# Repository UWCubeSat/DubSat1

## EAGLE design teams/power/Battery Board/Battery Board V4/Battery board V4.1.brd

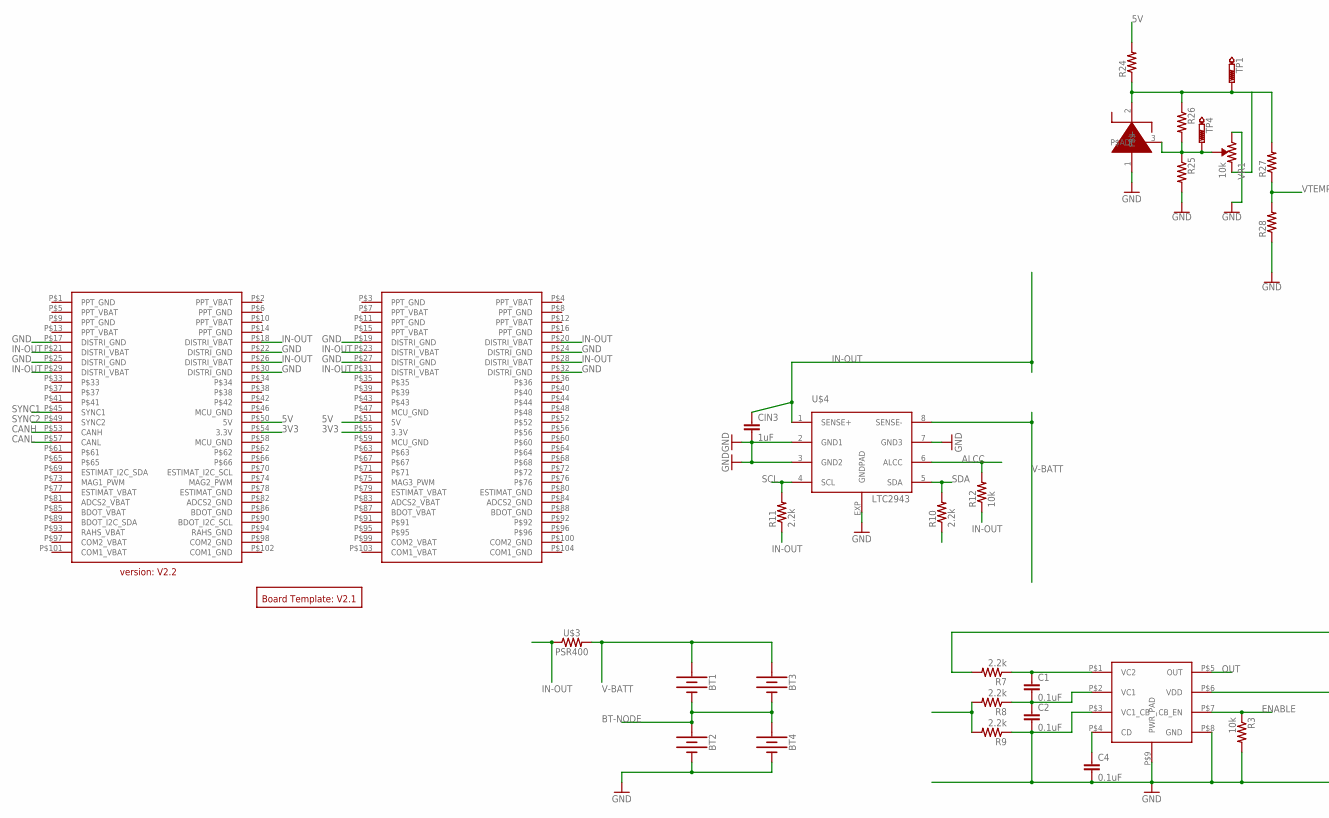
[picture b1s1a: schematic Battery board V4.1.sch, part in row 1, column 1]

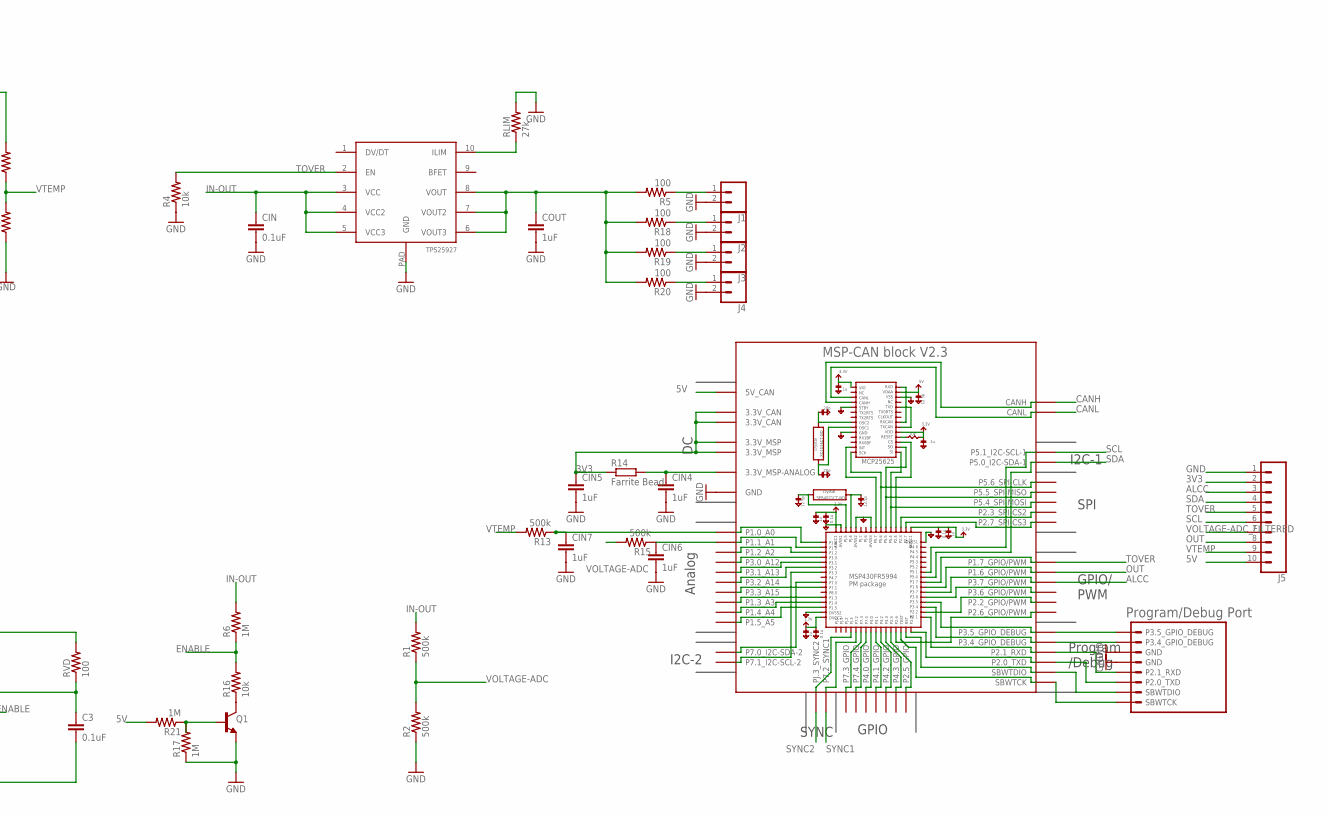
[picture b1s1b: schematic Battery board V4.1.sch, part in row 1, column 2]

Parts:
BT1, BT2, BT3, BT4: BATTERY-18650; BATTERY_18650-HOLDER
C1, C2, C3, C4: 0.1uF; C0805
CIN: 0.1uF; C0805
CIN3, CIN4, CIN5, CIN6, CIN7: 1uF; C0805
COUT: 1uF; C0805
J1, J2, J3, J4: CONN_02PTH3; 1X02_LONGPADS
J5: CONN_10LOCK; 1X10_LOCK
Q1: TRANS_NPN-MMBT2222AL; SOT23-3
R1, R2, R13, R15: 500k; R0805
R3, R4, R12, R16: 10k; R0805
R5, R18, R19, R20: 100; R0805
R6: 1M; R0805
R7, R8, R9, R10, R11: 2.2k; R0805
R14: Farrite Bead; R1206
R17, R21: 1M; M0805
R24, R25, R26, R27, R28: R-US_R0805; R0805
RLIM: 27k; R0805
RVD: 100; R0805
TP1, TP4: PTR1PAD1-13Y; P1-13Y
U$1: MSP-CAN_BLOCK
U$2: PROGRAM/DEBUG_PORT; 1X08_CONNECTOR
U$3: PSR400
U$4: LTC2943; DFN8(3X3)LT
U$5: TPS252927; VSON10
U$7: 2X26_CONNECTOR_(V2.2); 4X26_CONNECTOR_(V2.2)
U$8: BQ29209; VSON8
U$9: BOARD_TEMPLATE_(V2.1)
U$10: LM135Z; TO-92-3
VR1: 10k; TRIMPOT-SMD-TC33X

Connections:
3V3: CIN5.1, J5.2, R14.1, U$1.3.3V@CAN1 (3.3V_CAN), U$1.3.3V@CAN2 (3.3V_CAN), U$1.3.3V@MSP1 (3.3V_MSP), U$1.3.3V@MSP2 (3.3V_MSP), U$7.P$54 (3.3V), U$7.P$55 (3.3V)
5V: J5.10, R21.2, R24.2, U$1.5V (5V_CAN), U$7.P$50 (5V), U$7.P$51 (5V)
ALCC: J5.3, R12.2, U$1.P3.7_GPIO/PWM, U$4.6 (ALCC)
BASE: Q1.1 (B), R17.2, R21.1
BT-NODE: BT1.GND@1 (-), BT2.PWR@1 (+), BT3.GND@1 (-), BT4.PWR@1 (+), R8.2, R9.2
CANH: U$1.CANH, U$7.P$53 (CANH)
CANL: U$1.CANL, U$7.P$57 (CANL)
ENABLE: R3.1, R6.1, R16.2, U$8.P$7 (CB_EN)
FERRITE-BEAD: CIN4.1, R14.2, U$1.3.3V_ANALOG@MSP2 (3.3V_MSP-ANALOG)
GND: BT2.GND@1 (-), BT4.GND@1 (-), C2.2, C3.2, C4.2, CIN.2, CIN3.2, CIN4.2, CIN5.2, CIN6.2, CIN7.2, COUT.2, J1.2, J2.2, J3.2, J4.2, J5.1, Q1.2 (E), R2.1, R3.2, R4.1, R9.1, R17.1, R25.2, R28.1, RLIM.2, U$1.GND@1 (GND), U$1.GND@2 (GND), U$1.GND@3 (GND), U$1.GND@4 (GND), U$1.GND@5 (GND), U$1.GND@7 (GND), U$1.GND@8 (GND), U$1.GND@9 (GND), U$1.GND@10 (GND), U$1.GND@11 (GND), U$1.GND@12 (GND), U$1.GND@13 (GND), U$1.GND@14 (GND), U$1.GND@15 (GND), U$1.GND@16 (GND), U$1.GND@17 (GND), U$1.GND@26 (GND), U$2.5 (GND), U$2.6 (GND), U$4.2 (GND1), U$4.3 (GND2), U$4.7 (GND3), U$4.EXP (GNDPAD), U$5.PAD (GND), U$7.P$17 (DISTRI_GND), U$7.P$19 (DISTRI_GND), U$7.P$22 (DISTRI_GND), U$7.P$24 (DISTRI_GND), U$7.P$25 (DISTRI_GND), U$7.P$27 (DISTRI_GND), U$7.P$30 (DISTRI_GND), U$7.P$32 (DISTRI_GND), U$8.P$3 (VC1_CB), U$8.P$8 (GND), U$8.P$9 (PWR_PAD), U$10.1 (P$-), VR1.1 (CW)
HEATER1: J3.1, R19.1
IN-OUT: CIN.1, CIN3.1, R1.2, R6.2, R7.2, R10.1, R11.1, R12.1, RVD.2, U$3.P$1 (1), U$4.1 (SENSE+), U$5.3 (VCC), U$5.4 (VCC2), U$5.5 (VCC3), U$7.P$18 (DISTRI_VBAT), U$7.P$20 (DISTRI_VBAT), U$7.P$21 (DISTRI_VBAT), U$7.P$23 (DISTRI_VBAT), U$7.P$26 (DISTRI_VBAT), U$7.P$28 (DISTRI_VBAT), U$7.P$29 (DISTRI_VBAT), U$7.P$31 (DISTRI_VBAT)
unnamed: J1.1, R5.1
unnamed: C1.1, R7.1, U$8.P$1 (VC2)
unnamed: C1.2, C2.1, R8.1, U$8.P$2 (VC1)
unnamed: C3.1, RVD.1, U$8.P$6 (VDD)
unnamed: Q1.3 (C), R16.1
unnamed: C4.1, U$8.P$4 (CD)
unnamed: COUT.1, R5.2, R18.2, R19.2, R20.2, U$5.6 (VOUT3), U$5.7 (VOUT2), U$5.8 (VOUT)
unnamed: RLIM.1, U$5.10 (ILIM)
unnamed: J2.1, R18.1
unnamed: J4.1, R20.1
unnamed: U$1.P3.5_GPIO_DEBUG, U$2.8 (P3.5_GPIO_DEBUG)
unnamed: U$1.P3.4_GPIO_DEBUG, U$2.7 (P3.4_GPIO_DEBUG)
unnamed: U$1.P2.1_RXD, U$2.4 (P2.1_RXD)
unnamed: U$1.P2.0_TXD, U$2.3 (P2.0_TXD)
unnamed: U$1.SBWTDIO, U$2.2 (SBWTDIO)
unnamed: U$1.SBWTCK, U$2.SBWTCK
unnamed: R24.1, R26.1, R27.2, TP1.TP, U$10.2 (P$+), VR1.3 (CCW)
unnamed: R25.1, R26.2, TP4.TP, U$10.3 (P$ADJ), VR1.2 (WIPER)
OUT: J5.8, U$1.P1.6_GPIO/PWM, U$8.P$5 (OUT)
SCL: J5.6, R11.2, U$1.P5.1_I2C-SCL-1, U$4.4 (SCL)
SDA: J5.4, R10.2, U$1.P5.0_I2C-SDA-1, U$4.5 (SDA)
SYNC1: U$1.P7.2_SYNC1, U$7.P$45 (SYNC1)
SYNC2: U$1.PJ.3_SYNC2, U$7.P$49 (SYNC2)
TOVER: J5.5, R4.2, U$1.P1.7_GPIO/PWM, U$5.2 (EN)
V-BATT: BT1.PWR@1 (+), BT3.PWR@1 (+), U$3.P$2 (2), U$4.8 (SENSE-)
VOLTAGE-ADC: R1.1, R2.2, R15.2
VOLTAGE-ADC_FILTERED: CIN6.1, J5.7, R15.1, U$1.P1.1_A1
VTEMP: J5.9, R13.2, R27.1, R28.2
VTEMP_FILTERED: CIN7.1, R13.1, U$1.P1.0_A0

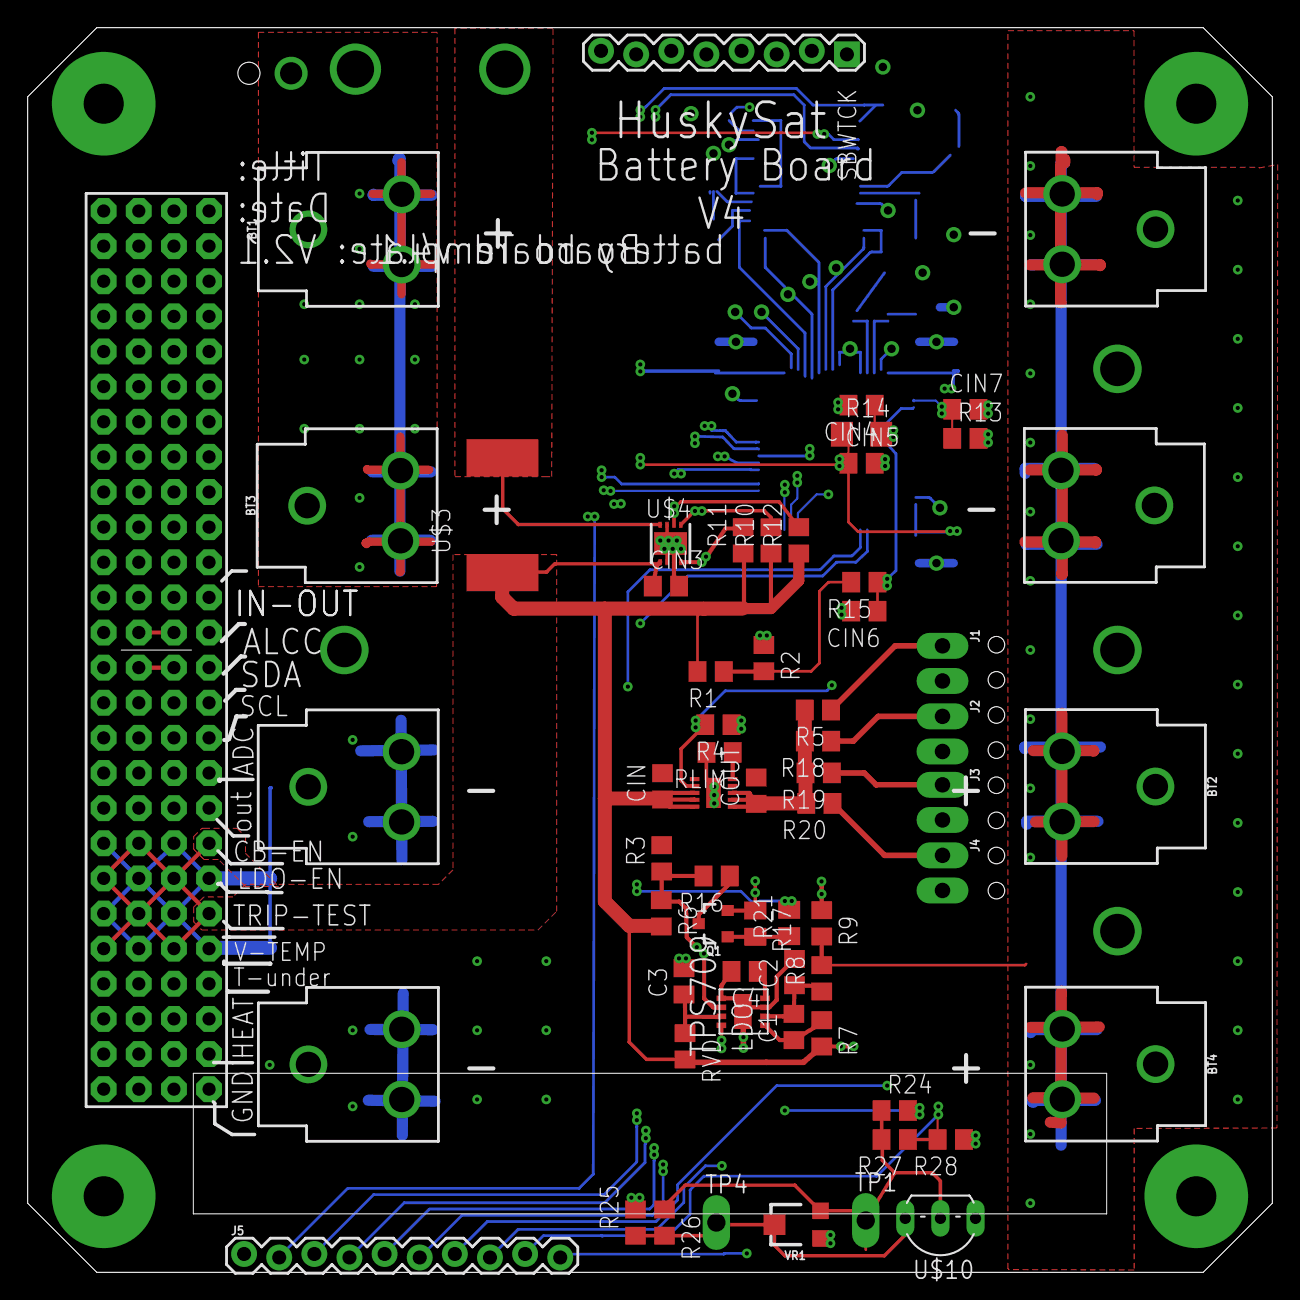
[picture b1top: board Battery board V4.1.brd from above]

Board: 4 copper layers, 90.0 x 90.0 mm, 61 parts (1 on the bottom side), 41 nets.

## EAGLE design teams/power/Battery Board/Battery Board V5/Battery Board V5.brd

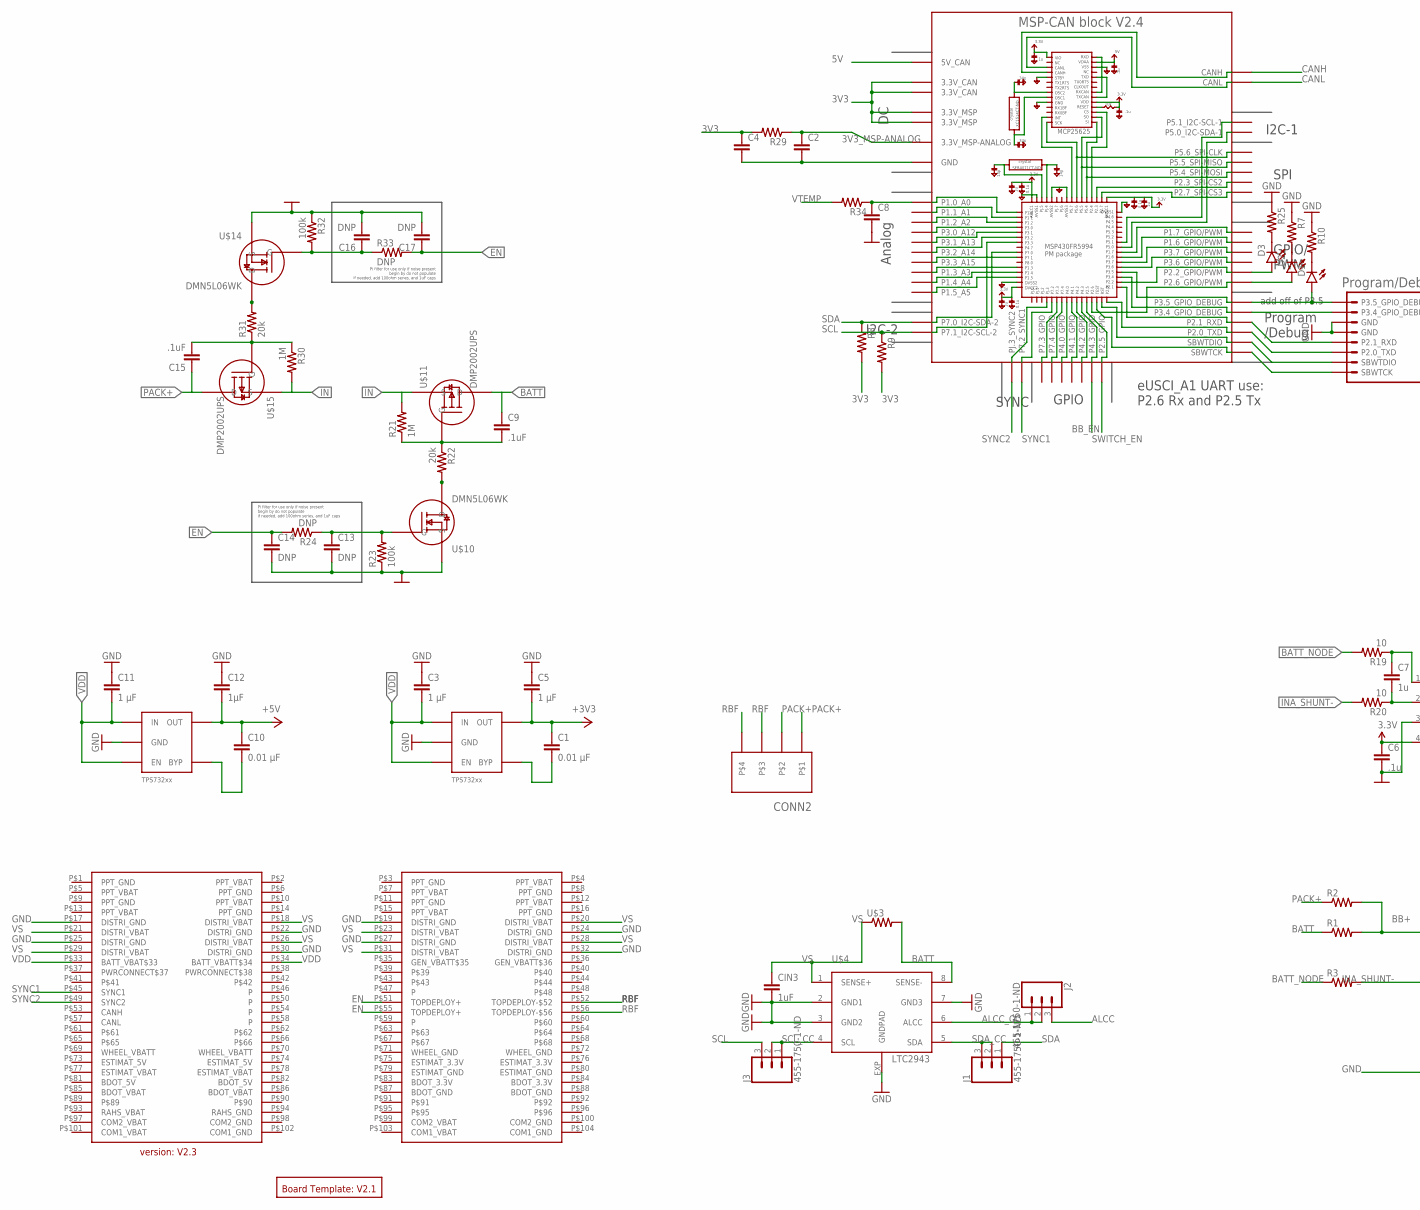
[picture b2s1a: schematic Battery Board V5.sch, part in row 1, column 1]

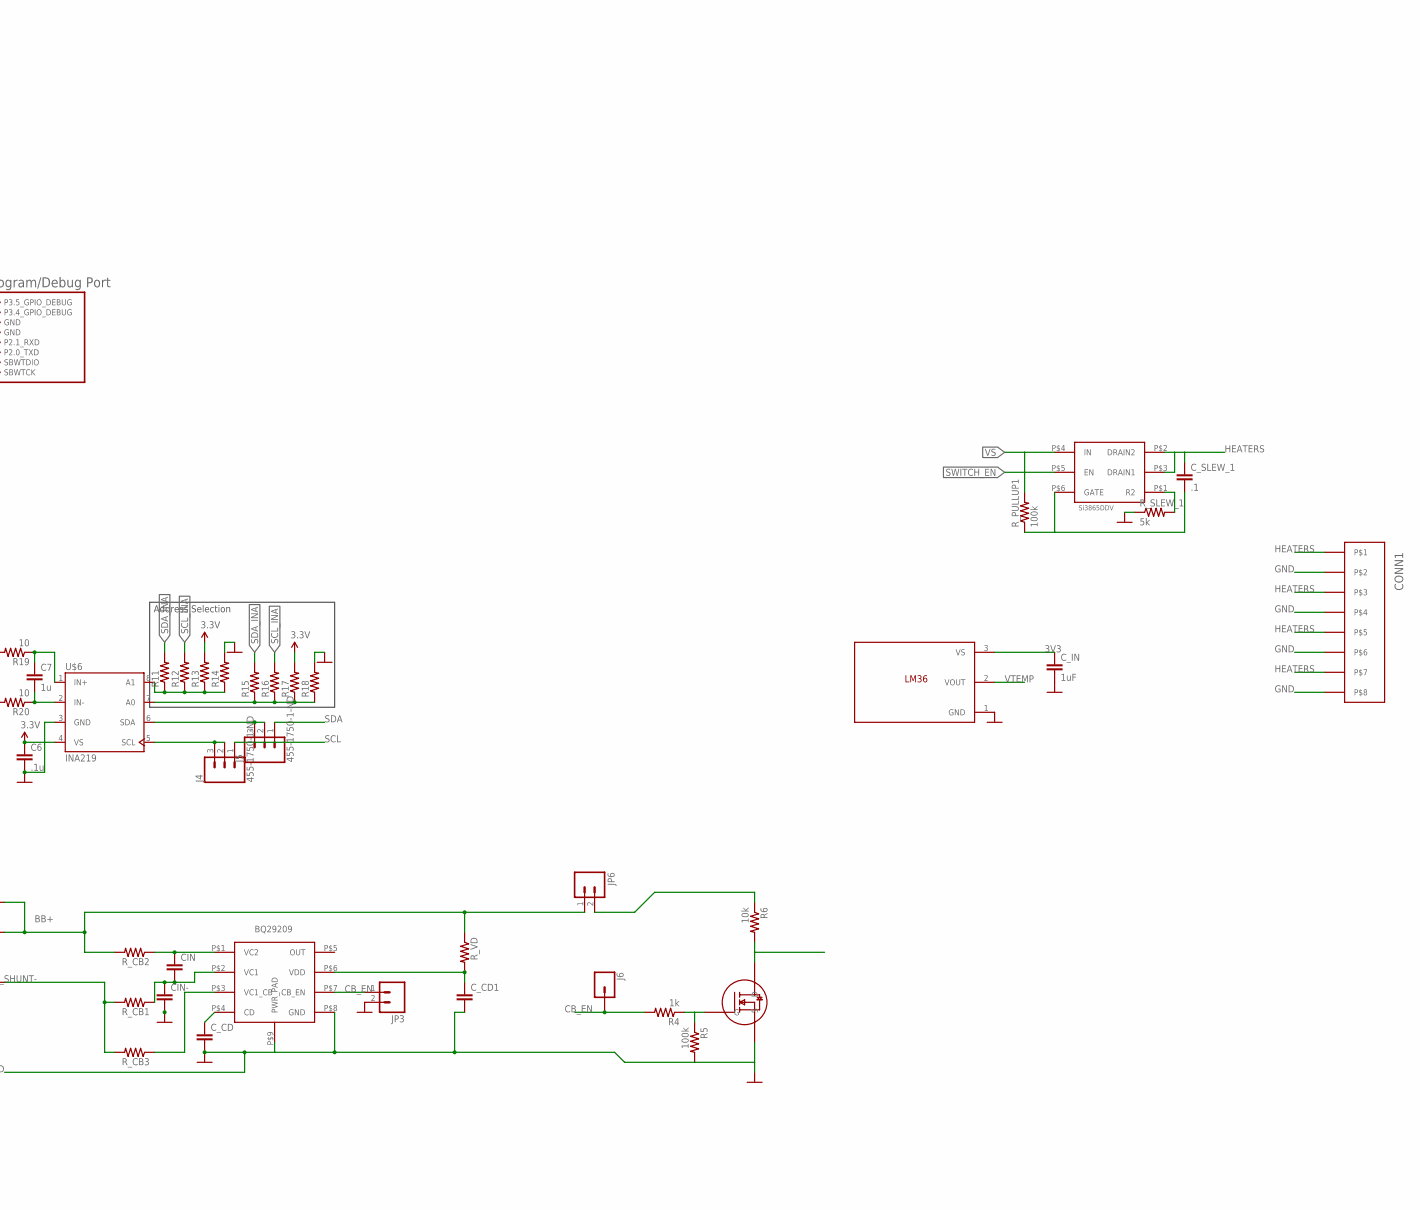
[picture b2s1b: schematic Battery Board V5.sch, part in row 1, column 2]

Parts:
BLK1: MSP-CAN_BLOCK
C1, C10: 0.01 μF; 0805
C2, C4, C8: CAPACITOR0805; 0805
C3, C5, C11: 1 μF; 0805
C6: .1u; 0805
C7: 1u; 0805
C9, C15: .1uF; 0805
C12: 1μF; 0805
C13, C14, C16, C17: DNP; 0805
CIN: CAPACITOR0805; 0805
CIN3: 1uF; C0805
CIN-: CAPACITOR0805; 0805
CONN1: PICOLOCK_8
CONN2: PICOLOCK_4
C_CD, C_CD1: CAPACITOR0805; 0805
C_IN: 1uF; 0805
C_SLEW_1: .1; 0805
D1, D2, D3: LED; LED-1206
J1, J2, J3, J4, J5: 455-1750-1-ND; 1X03
J6: CONN_01; 1X01
JP3, JP6: M02LOCK; 1X02_LOCK
R1, R2, R7, R8, R9, R10, R11, R12, R13, R14, R15, R16, R17, R18, R25, R29, R34: RESISTOR0805; 0805
R3: RESISTOR2010; R2010
R4: 1k; 0805
R5, R23, R32: 100k; 0805
R6: 10k; 0805
R19, R20: 10; 0805
R21, R30: 1M; 0805
R22, R31: 20k; 0805
R24, R33: DNP; 0805
R_CB1, R_CB2, R_CB3: RESISTOR0805; 0805
R_PULLUP1: 100k; 0805
R_SLEW_1: 5k; 0805
R_VD: RESISTOR0805; 0805
U1, U4: TPS732XX; SOT-23-5
U$1: BOARD_TEMPLATE1; BOARD_TEMPLATE
U$2: PC104_CONNECTOR
U$3: RESISTOR2512; R2512
U$4: LTC2943; DFN8(3X3)LT
U$5: BQ29209; VSON8
U$6: INA219; SOT-23-8
U$7: DMN62D0U; SOT-23-3
U$8: LM36; TO-92-3
U$10, U$14: DMN5L06WK; SOT-323
U$11, U$15: DMP2002UPS; POWERDI5060-8
U$12: PROGRAM/DEBUG_PORT; 1X08_CONNECTOR
U$16: SI3865DDV; TSOP-6

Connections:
3V3: BLK1.3.3V@CAN1 (3.3V_CAN), BLK1.3.3V@CAN2 (3.3V_CAN), BLK1.3.3V@MSP1 (3.3V_MSP), BLK1.3.3V@MSP2 (3.3V_MSP), C1.1, C4.1, C5.2, C6.1, C_IN.1, R8.2, R9.2, R13.2, R17.2, R29.2, U1.P$5 (OUT), U$6.4 (VS), U$8.3 (VS)
3V3_MSP-ANALOG: BLK1.3.3V_ANALOG@MSP2 (3.3V_MSP-ANALOG), C2.1, R29.1
5V: BLK1.5V (5V_CAN), C10.1, C12.2, U4.P$5 (OUT)
ALCC: J2.3
ALCC_CC: J2.1, J2.2, U$4.6 (ALCC)
BATT: C9.1, R1.1, U$3.2, U$4.8 (SENSE-), U$11.D1 (D), U$11.D2 (D), U$11.D3 (D), U$11.D4 (D), U$11.D5 (D)
BATT_NODE: R3.1, R19.2
BB+: JP6.1, R1.2, R2.2, R_CB2.2, R_VD.1
BB_EN: BLK1.P4.3_GPIO, R6.2, U$7.3 (D)
CANH: BLK1.CANH
CANL: BLK1.CANL
CB_EN: J6.1, JP3.1, R4.2, U$5.P$7 (CB_EN)
EN: C14.1, C17.1, R24.2, R33.2, U$2.P$51 (TOPDEPLOY+), U$2.P$55 (TOPDEPLOY+)
GND: BLK1.GND@1 (GND), BLK1.GND@2 (GND), BLK1.GND@3 (GND), BLK1.GND@4 (GND), BLK1.GND@5 (GND), BLK1.GND@7 (GND), BLK1.GND@8 (GND), BLK1.GND@9 (GND), BLK1.GND@10 (GND), BLK1.GND@11 (GND), BLK1.GND@12 (GND), BLK1.GND@13 (GND), BLK1.GND@14 (GND), BLK1.GND@15 (GND), BLK1.GND@16 (GND), BLK1.GND@17 (GND), BLK1.GND@26 (GND), C2.2, C3.1, C4.2, C5.1, C6.2, C8.2, C11.1, C12.1, C13.2, C14.2, C16.2, C17.2, CIN3.2, CIN-.2, CONN1.P$2, CONN1.P$4, CONN1.P$6, CONN1.P$8, C_CD.2, C_CD1.2, C_IN.2, JP3.2, R5.2, R7.1, R10.1, R14.2, R18.2, R23.1, R25.1, R32.1, R_SLEW_1.1, U1.P$2 (GND), U4.P$2 (GND), U$2.P$17 (DISTRI_GND), U$2.P$19 (DISTRI_GND), U$2.P$22 (DISTRI_GND), U$2.P$24 (DISTRI_GND), U$2.P$25 (DISTRI_GND), U$2.P$27 (DISTRI_GND), U$2.P$30 (DISTRI_GND), U$2.P$32 (DISTRI_GND), U$4.2 (GND1), U$4.3 (GND2), U$4.7 (GND3), U$4.EXP (GNDPAD), U$5.P$8 (GND), U$5.P$9 (PWR_PAD), U$6.3 (GND), U$7.2 (S), U$8.1 (GND), U$10.2 (S), U$12.5 (GND), U$12.6 (GND), U$14.2 (S)
HEATERS: CONN1.P$1, CONN1.P$3, CONN1.P$5, CONN1.P$7, C_SLEW_1.1, U$16.P$2 (DRAIN2), U$16.P$3 (DRAIN1)
IN: R21.2, R30.2, U$11.S1 (S), U$11.S2 (S), U$11.S3 (S), U$15.S1 (S), U$15.S2 (S), U$15.S3 (S)
INA219_A0_1: R15.1, R16.1, R17.1, R18.1, U$6.7 (A0)
INA219_A1_1: R11.1, R12.1, R13.1, R14.1, U$6.8 (A1)
INA219_IN+_1: C7.1, R19.1, U$6.1 (IN+)
INA219_IN-_1: C7.2, R20.1, U$6.2 (IN-)
INA_SHUNT-: R3.2, R20.2, R_CB1.2, R_CB3.2
LDO_3V3_BYP1: C1.2, U1.P$4 (BYP)
LDO_5V_BYP1: C10.2, U4.P$4 (BYP)
unnamed: BLK1.P3.5_GPIO_DEBUG, D1.A, U$12.8 (P3.5_GPIO_DEBUG)
unnamed: JP6.2, R6.1
unnamed: BLK1.P3.4_GPIO_DEBUG, U$12.7 (P3.4_GPIO_DEBUG)
unnamed: BLK1.P2.1_RXD, U$12.4 (P2.1_RXD)
unnamed: CIN.1, R_CB2.1, U$5.P$1 (VC2)
unnamed: CIN.2, CIN-.1, R_CB1.1, U$5.P$2 (VC1)
unnamed: C9.2, R21.1, R22.1, U$11.G
unnamed: C13.1, R23.2, R24.1, U$10.1 (G)
unnamed: R_CB3.1, U$5.P$3 (VC1_CB)
unnamed: C_CD.1, U$5.P$4 (CD)
unnamed: R22.2, U$10.3 (D)
unnamed: R4.1, R5.1, U$7.1 (G)
unnamed: C_CD1.1, R_VD.2, U$5.P$6 (VDD)
unnamed: C15.2, R30.1, R31.1, U$15.G
unnamed: C16.1, R32.2, R33.1, U$14.1 (G)
unnamed: R31.2, U$14.3 (D)
unnamed: BLK1.P2.0_TXD, U$12.3 (P2.0_TXD)
unnamed: BLK1.SBWTDIO, U$12.2 (SBWTDIO)
unnamed: BLK1.SBWTCK, U$12.SBWTCK
unnamed: D1.C, R10.2
unnamed: BLK1.P1.0_A0, C8.1, R34.1
unnamed: D2.C, R7.2
unnamed: D3.C, R25.2
unnamed: R_SLEW_1.2, U$16.P$1 (R2)
unnamed: C_SLEW_1.2, R_PULLUP1.1, U$16.P$6 (GATE)
unnamed: BLK1.P2.2_GPIO/PWM, D3.A
unnamed: BLK1.P2.6_GPIO/PWM, D2.A
PACK+: C15.1, CONN2.P$1, CONN2.P$2, R2.1, U$15.D1 (D), U$15.D2 (D), U$15.D3 (D), U$15.D4 (D), U$15.D5 (D)
RBF: CONN2.P$3, CONN2.P$4, U$2.P$52 (TOPDEPLOY-$52), U$2.P$56 (TOPDEPLOY-$56)
SCL: BLK1.P7.1_I2C-SCL-2, J3.3, J4.1, R9.1
SCL_CC: J3.1, J3.2, U$4.4 (SCL)
SCL_INA: J4.2, J4.3, R12.2, R16.2, U$6.5 (SCL)
SDA: BLK1.P7.0_I2C-SDA-2, J1.1, J5.1, R8.1
SDA_CC: J1.2, J1.3, U$4.5 (SDA)
SDA_INA: J5.2, J5.3, R11.2, R15.2, U$6.6 (SDA)
SWITCH_EN: BLK1.P2.5_GPIO, U$16.P$5 (EN)
SYNC1: BLK1.P7.2_SYNC1, U$2.P$45 (SYNC1)
SYNC2: BLK1.PJ.3_SYNC2, U$2.P$49 (SYNC2)
VDD: C3.2, C11.2, U1.P$1 (IN), U1.P$3 (EN), U4.P$1 (IN), U4.P$3 (EN), U$2.P$33 (BATT_VBAT$33), U$2.P$34 (BATT_VBATT$34)
VS: CIN3.1, R_PULLUP1.2, U$2.P$18 (DISTRI_VBAT), U$2.P$20 (DISTRI_VBAT), U$2.P$21 (DISTRI_VBAT), U$2.P$23 (DISTRI_VBAT), U$2.P$26 (DISTRI_VBAT), U$2.P$28 (DISTRI_VBAT), U$2.P$29 (DISTRI_VBAT), U$2.P$31 (DISTRI_VBAT), U$3.1, U$4.1 (SENSE+), U$16.P$4 (IN)
VTEMP: R34.2, U$8.2 (VOUT)

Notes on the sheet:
Address Selection
Pi filter for use only if noise present begin by do not populate if needed, add 100ohm series, and 1uF caps

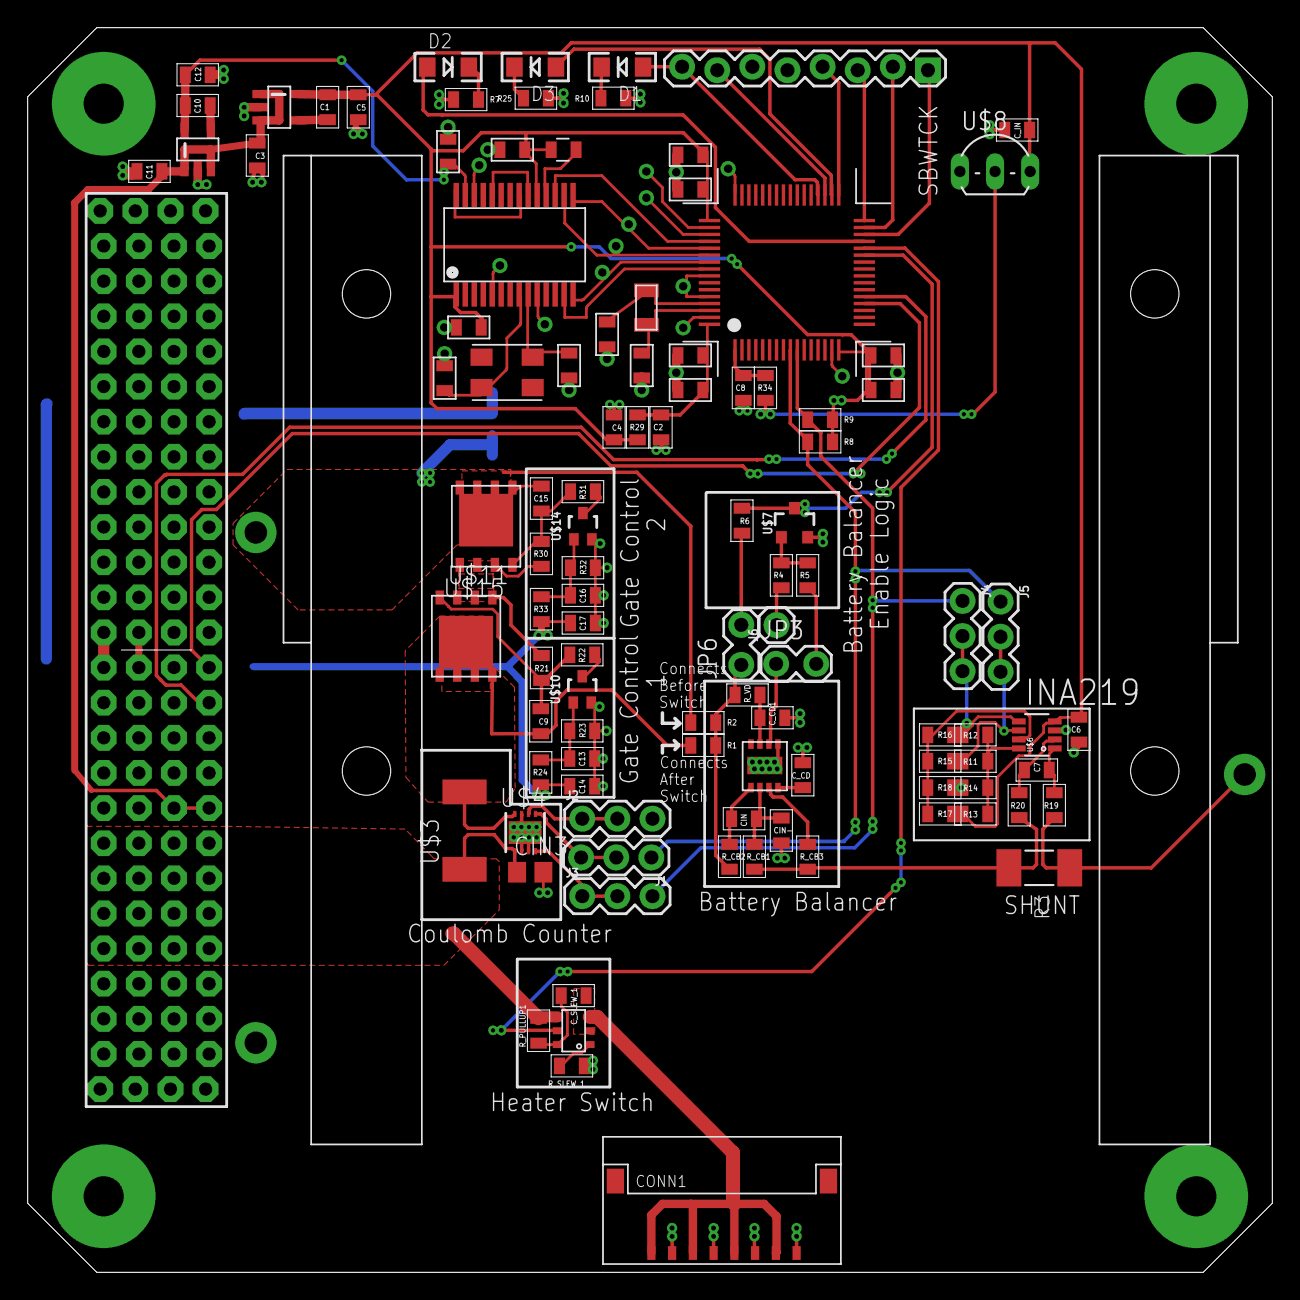
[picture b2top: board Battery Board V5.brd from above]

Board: 2 copper layers, 90.0 x 90.0 mm, 92 parts (1 on the bottom side), 61 nets.

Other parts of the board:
U$9: BATTERY_HOLDERS

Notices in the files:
parts and their libraries:
SparkFun-Batteries: Licensing: Creative Commons ShareAlike 4.0 International - https://creativecommons.org/licenses/by-sa/4.0
